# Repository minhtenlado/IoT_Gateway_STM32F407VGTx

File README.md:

# STM32F407 IoT Gateway — 6-Layer PCB

**Custom industrial IoT gateway** based on the **STM32F407VGTx**, designed in **KiCad 10** with Wi-Fi, Ethernet, isolated RS485, four relay outputs, external SPI Flash and an onboard USB-C debug-probe circuit.

> [!IMPORTANT]
> **Trạng thái dự án:** Đã có **schematic, PCB layout 6 lớp, ảnh 3D, Gerber, BOM và mã nguồn firmware debug tham khảo**. Chưa có xác nhận bo mạch đã được lắp ráp, thử nghiệm điện hoặc kiểm chứng đầy đủ ERC/DRC. Không coi các file sản xuất là bằng chứng thiết kế đã sẵn sàng để chế tạo hàng loạt.
>
> **Firmware trong `firrmware_STLINKV2/` là dự án [dap42](https://github.com/devanlai/dap42) (CMSIS-DAP nguồn mở), không phải firmware ST-LINK/V2 chính hãng của STMicroelectronics.** Chưa xác nhận firmware này chạy trên PCB hiện tại mà không chỉnh sửa.

## 1. PCB 3D Preview

Các hình sau được xuất từ **project KiCad của bo mạch này**. Nhấn vào hình để mở ảnh gốc với độ phân giải cao.

### Góc nhìn tổng thể

[.png>)](<images/IoT_gateway_STM32F407(1).png>)

### Hai góc nhìn 3D bổ sung

| 3D View 01 | 3D View 02 |
| :---: | :---: |
|  | [.png>)](<images/IoT_gateway_STM32F407(2).png>) |

## 2. PCB Layout — 6 Copper Layers

PCB sử dụng **6 lớp đồng**: `F.Cu`, `In1.Cu`, `In2.Cu`, `In3.Cu`, `In4.Cu`, `B.Cu`. Các hình bên dưới là ảnh từng lớp riêng biệt, đã lưu trong thư mục [`images/`](images/).

| Front Copper — `F.Cu` | Inner Copper 1 — `In1.Cu` |
| :---: | :---: |
|  |  |

| Inner Copper 2 — `In2.Cu` | Inner Copper 3 — `In3.Cu` |
| :---: | :---: |
|  |  |

| Inner Copper 4 — `In4.Cu` | Back Copper — `B.Cu` |
| :---: | :---: |
|  |  |

### Tổng hợp các lớp đồng

### Bố trí footprint linh kiện

> **Lưu ý:** Các ảnh trên mô tả PCB theo file thiết kế, không phải ảnh bo mạch vật lý đã sản xuất.

## 3. System Architecture

```mermaid
flowchart TB
    PC["Computer"] -->|"USB-C / J2"| DBG["STM32F103CBT6 / U1<br/>Onboard CMSIS-DAP candidate"]
    DBG -. "SWD" .-> MCU["STM32F407VGTx / U3<br/>Main controller"]
    EXT["External SWD probe"] -->|"J1"| MCU
    VIN["12 V DC / J10"] --> POWER["DC/DC power supply"]
    POWER --> MCU
    POWER --> PERI["Peripheral power rails"]
    MCU <-->|"UART"| WIFI["ESP32-C3 Wi-Fi"]
    MCU <-->|"RMII"| ETH["LAN8720A PHY"]
    ETH --- RJ45["RJ45 / J3"]
    MCU <-->|"UART"| RS485["Isolated RS485"]
    MCU --> DRV["ULN2003A"] --> RLY["4 relay channels"]
    MCU <-->|"SPI"| FLASH["W25Q128 Flash"]
    MCU <-->|"I2C / peripherals"| SENS["TMP1075 + INA226"]
    MCU --- GPIO["GPIO headers"]
```

Sơ đồ khối thể hiện **kiến trúc thiết kế**; các giao tiếp chưa được xác nhận hoạt động trên phần cứng thực tế.

## 4. Hardware Overview

| Khối chức năng | Linh kiện / đầu nối | Vai trò |
| --- | --- | --- |
| Main MCU | **U3 — STM32F407VGTx** | Bộ điều khiển trung tâm, ARM Cortex-M4 |
| Onboard debug MCU | **U1 — STM32F103CBT6** | MCU dùng cho mạch USB-to-SWD dự kiến |
| Wireless | **U14 — ESP32-C3-WROOM-02U** | Wi-Fi, giao tiếp với MCU chính |
| Ethernet | **U6 — LAN8720A**, **J3 — HR911105A** | Ethernet PHY 10/100 Mbps và cổng RJ45 |
| Industrial bus | **U10 — ADM2861EBRNZ** | Truyền thông RS485 cách ly |
| Relay outputs | **K1–K4**, **U11 — ULN2003A** | 4 kênh relay có mạch driver |
| External Flash | **U4 — W25Q128JVS** | SPI NOR Flash |
| Temperature | **U12 — TMP1075D** | Giám sát nhiệt độ |
| Power monitoring | **U13 — INA226**, **R56 — 20 mΩ** | Đo điện áp và dòng điện qua shunt |
| RTC backup | **BT1** | Vị trí pin dự phòng |
| Expansion | **J4, J11, J12** | Header GPIO mở rộng |
| System power | **J10** | Nguồn DC 12 V cho hệ thống |
| Debug USB | **J2** | USB Type-C kết nối với U1 |
| External programming | **J1** | Header SWD nạp trực tiếp U3 |

### Power architecture

Các khối nguồn trên schematic gồm **AP63203WU (U7)**, **AP63205WU (U8)** và **AP2112K-3.3 (U9)**. Các net chính bao gồm `+12V_PROTECTED`, `+5V_BUCK`, `+3V3_SYS` và `+3V3_STLINK`.

> [!WARNING]
> **USB-C/J2 không được mặc định là nguồn cấp cho toàn bộ bo mạch.** Theo cấu trúc hiện tại, J2 phục vụ khối debug U1, còn U3 và hệ thống cần nguồn phù hợp từ đường DC 12 V. Phải kiểm tra sơ đồ nguồn trước khi nạp/debug hoặc nối nguồn đồng thời.

## 5. STM32 Programming & Debugging

Có **hai đường nạp/debug khác nhau** cho STM32F407 (U3).

### A. External ST-Link / CMSIS-DAP via J1

**J1 là cổng SWD dành cho U3 (STM32F407VGTx), không phải cổng nạp U1.**

| SWD signal | Target U3 |
| --- | --- |
| SWDIO / `T_DIO` | PA13 |
| SWCLK / `T_CLK` | PA14 |
| NRST / `T_RST` | NRST |
| GND | GND |
| VTref | 3.3 V target logic reference |

Cấp nguồn cho bo mạch theo thiết kế, sau đó kết nối một probe SWD bên ngoài với **J1 theo tên net trên schematic**. Dùng **STM32CubeProgrammer** với ST-Link chính hãng hoặc phần mềm tương thích với probe đang sử dụng. Không suy luận thứ tự chân J1 từ bảng này.

### B. Onboard USB-C debug via J2 and U1

Đường tín hiệu dự kiến:

`Computer → USB-C (J2) → STM32F103CBT6 (U1) → SWD → STM32F407VGTx (U3)`

| SWD signal | U1 — Debug MCU | U3 — Main MCU |
| --- | --- | --- |
| SWDIO / `T_DIO` | PB14 | PA13 |
| SWCLK / `T_CLK` | PB13 | PA14 |
| Reset / `T_RST` | PB0 | NRST |
| SWO / `T_SWO` | PA10 (theo schematic) | PB3 |

Để mạch debug onboard hoạt động, cần nạp và cấu hình firmware thích hợp vào U1, bảo đảm clock USB/SWD, reset, pin mapping và nguồn logic. **Không thể chỉ hàn STM32F103 mới lên PCB rồi cắm USB-C để máy tính tự nhận ST-Link.**

## 6. Onboard Debugger Firmware — dap42 / CMSIS-DAP

Mã nguồn được lưu tại [`firrmware_STLINKV2/`](firrmware_STLINKV2/) (**giữ nguyên tên thư mục hiện tại, bao gồm cách viết `firrmware`**).

> [!IMPORTANT]
> Thư mục trên chứa **[dap42](https://github.com/devanlai/dap42)**, một dự án **CMSIS-DAP open-source** hỗ trợ STM32F042/STM32F103 và có các cấu hình dành cho **phần cứng ST-LINK/V2 hoặc ST-LINK/V2-1**. Tên thư mục không có nghĩa đây là firmware ST-LINK/V2 chính hãng. Sau khi nạp dap42, probe hoạt động theo giao thức **CMSIS-DAP** (ví dụ với OpenOCD), **không phải thiết bị ST-Link chính hãng trong STM32CubeProgrammer**.

### Những gì có sẵn trong thư mục firmware

| Đường dẫn | Nội dung |
| --- | --- |
| [`firrmware_STLINKV2/src/`](firrmware_STLINKV2/src/) | Mã nguồn C cho CMSIS-DAP, USB, cấu hình phần cứng |
| [`firrmware_STLINKV2/src/targets.mk`](firrmware_STLINKV2/src/targets.mk) | Các target STM32F103, STLINKV2-DONGLE, STLINKV2-1 |
| [`firrmware_STLINKV2/Makefile`](firrmware_STLINKV2/Makefile) | Build targets và xuất firmware `.bin` |
| [`firrmware_STLINKV2/openocd/`](firrmware_STLINKV2/openocd/) | Cấu hình OpenOCD tham khảo |
| [`firrmware_STLINKV2/FLASHING.md`](firrmware_STLINKV2/FLASHING.md) | Hướng dẫn nạp firmware dap42 |
| [`firrmware_STLINKV2/README.md`](firrmware_STLINKV2/README.md) | Tài liệu dự án dap42 gốc |
| [`firrmware_STLINKV2/LICENSE`](firrmware_STLINKV2/LICENSE) | Giấy phép phần mềm của dự án dap42 |

**Khả năng phù hợp với PCB này:** Các đường `PB14 → SWDIO`, `PB13 → SWCLK` và `PB0 → NRST` của U1 tương ứng với cấu hình STM32F103 kiểu `stlinkv2-1` trong dap42. **Tuy nhiên, đường SWO trên schematic là `PA10` trong khi cấu hình mẫu dùng `PB11`;** ngoài ra còn phải kiểm tra USB pull-up, LED, GPIO khác và 8 MHz HSE trước khi flash. Chưa có bản firmware được chứng minh là tương thích toàn bộ pinout của PCB.

### Build firmware (tham khảo, chưa xác nhận cho PCB này)

Mã nguồn dap42 dùng **libopencm3**. Bản RAR được cung cấp **chưa chứa mã nguồn dependency này** trong thư mục `libopencm3/`; cần tải bổ sung trước khi build:

```bash
cd firrmware_STLINKV2
# Chỉ cần thực hiện khi thư mục libopencm3 chưa có mã nguồn
git clone https://github.com/libopencm3/libopencm3.git libopencm3

# Yêu cầu: GNU make và ARM GNU Toolchain (arm-none-eabi-*)
# Build ví dụ cho phần cứng profile ST-LINK/V2-1 tham khảo:
make DAP103-NUCLEO.bin
```

Bản `.bin` sinh ra bởi lệnh trên **không được khuyến nghị nạp trực tiếp lên U1** trước khi đối chiếu và điều chỉnh file `src/stm32f103/stlinkv2-1/target.c`, `config.h`, thiết lập clock và chân của PCB. Cần phương pháp **nạp lần đầu cho U1** bằng SWD hoặc bootloader thích hợp; **J1 chỉ phục vụ U3**.

**Upstream & licensing:** [devanlai/dap42](https://github.com/devanlai/dap42) · [dap42 hardware](https://github.com/devanlai/dap42-hardware) · [libopencm3](https://github.com/libopencm3/libopencm3). Mã nguồn bao gồm thành phần mang giấy phép ISC, Apache-2.0 và LGPLv3; khi phân phối phải tuân thủ các giấy phép kèm theo từng thành phần.

## 7. ESP32-C3 Wi-Fi

Module **ESP32-C3-WROOM-02U** cung cấp chức năng Wi-Fi. Header **J13 (`ESP32_UART0_PROG`)** trên schematic phục vụ UART0 để lập trình và kiểm tra module. Khi sử dụng bộ chuyển USB–UART ngoài, phải kiểm tra điện áp logic 3.3 V và chế độ boot thực tế.

## 8. Project Structure

```text
IoT_gateway_STM32F407/
├── README.md
├── IoT_gateway_STM32F407.kicad_pro      # KiCad project
├── IoT_gateway_STM32F407.kicad_sch      # Schematic
├── IoT_gateway_STM32F407.kicad_pcb      # 6-layer PCB layout
├── Schematic.pdf                       # PDF schematic
├── images/
│   ├── IoT_gateway_STM32F407.png       # 3D render
│   ├── IoT_gateway_STM32F407(1).png    # 3D render
│   ├── IoT_gateway_STM32F407(2).png    # 3D render
│   ├── F_cu.png
│   ├── In1_cu.png
│   ├── In2_cu.png
│   ├── In3_cu.png
│   ├── In4_cu.png
│   ├── B_cu.png
│   ├── F_in1_in2_in3_in4_B.png          # All layers preview
│   └── footprint.png                   # Component placement
├── production/
│   ├── IoT_gateway_STM32F407.zip       # Gerber + drill package
│   ├── bom.csv
│   ├── positions.csv
│   ├── designators.csv
│   └── netlist.ipc
├── firrmware_STLINKV2/                 # dap42 CMSIS-DAP source
│   ├── src/
│   ├── openocd/
│   ├── Makefile
│   ├── FLASHING.md
│   ├── LICENSE
│   └── README.md
└── library/                            # Custom symbols/footprints/models
```

### Quick links

- **[Mở thiết kế PCB KiCad](IoT_gateway_STM32F407.kicad_pcb)**
- **[Mở schematic KiCad](IoT_gateway_STM32F407.kicad_sch)** · **[Xem schematic PDF](Schematic.pdf)**
- **[Tải bộ Gerber + Drill](production/IoT_gateway_STM32F407.zip)**
- **[Xem BOM](production/bom.csv)** · **[Component placement](production/positions.csv)**
- **[Xem mã nguồn firmware CMSIS-DAP](firrmware_STLINKV2/)**
- **[Xem toàn bộ ảnh PCB](images/)**

## 9. Verification Checklist

- [x] Schematic được lưu trong project KiCad.
- [x] PCB layout **6 copper layers** đã có trong repository.
- [x] Đã xuất 3 ảnh 3D, 6 lớp đồng và 2 ảnh bổ sung.
- [x] Đã xuất Gerber/Drill, BOM và component placement files.
- [x] Có mã nguồn **dap42 CMSIS-DAP** làm firmware tham khảo cho U1.
- [x] Hoàn tất và xác nhận **ERC/DRC**, clearance, copper stackup, lớp cách ly.
- [ ] Kiểm tra đường nguồn 12 V, 5 V, 3.3 V và tách nguồn USB debug.
- [ ] Kiểm chứng thạch anh, USB, pin mapping và firmware CMSIS-DAP cho U1.
- [ ] Kiểm chứng Ethernet RMII/PHY, Wi-Fi, RS485, relay và cảm biến.
- [ ] Xác nhận quy trình nạp/khôi phục U1; thử nạp U3 qua U1 và qua debug onboard.
- [ ] Lắp prototype và thực hiện kiểm thử phần cứng trước khi sản xuất hàng loạt.

## 10. Safety & Licensing

- Không kết nối điện lưới AC hoặc tải công suất vào relay trước khi kiểm tra **clearance/creepage, cách ly, bảo vệ quá dòng, định mức relay và vỏ bảo vệ**.
- GPIO, UART, SWD phải dùng mức điện áp tương thích; không cấp 5 V vào chân logic 3.3 V nếu không được cho phép.
- File Gerber được cung cấp như **tài liệu thiết kế**, chưa phải chứng nhận đủ điều kiện sản xuất an toàn.
- **Phần cứng:** Chưa có file `LICENSE` riêng xác nhận giấy phép phát hành thiết kế PCB/schematic. Việc đăng lên GitHub không tự động chuyển quyền sử dụng phần cứng thành open-source hardware.
- **Firmware dap42:** Giữ nguyên thông báo bản quyền và các điều khoản trong [`firrmware_STLINKV2/LICENSE`](firrmware_STLINKV2/LICENSE) cũng như giấy phép thành phần phụ thuộc. Không hiểu nhầm đây là firmware chính hãng của ST.

---

**Designed by Phan Huynh Van Do** · **HW Rev 1.0 (design marking)** · **2026**

*STM32F407 IoT Gateway — custom embedded hardware for connected control and industrial interfaces.*

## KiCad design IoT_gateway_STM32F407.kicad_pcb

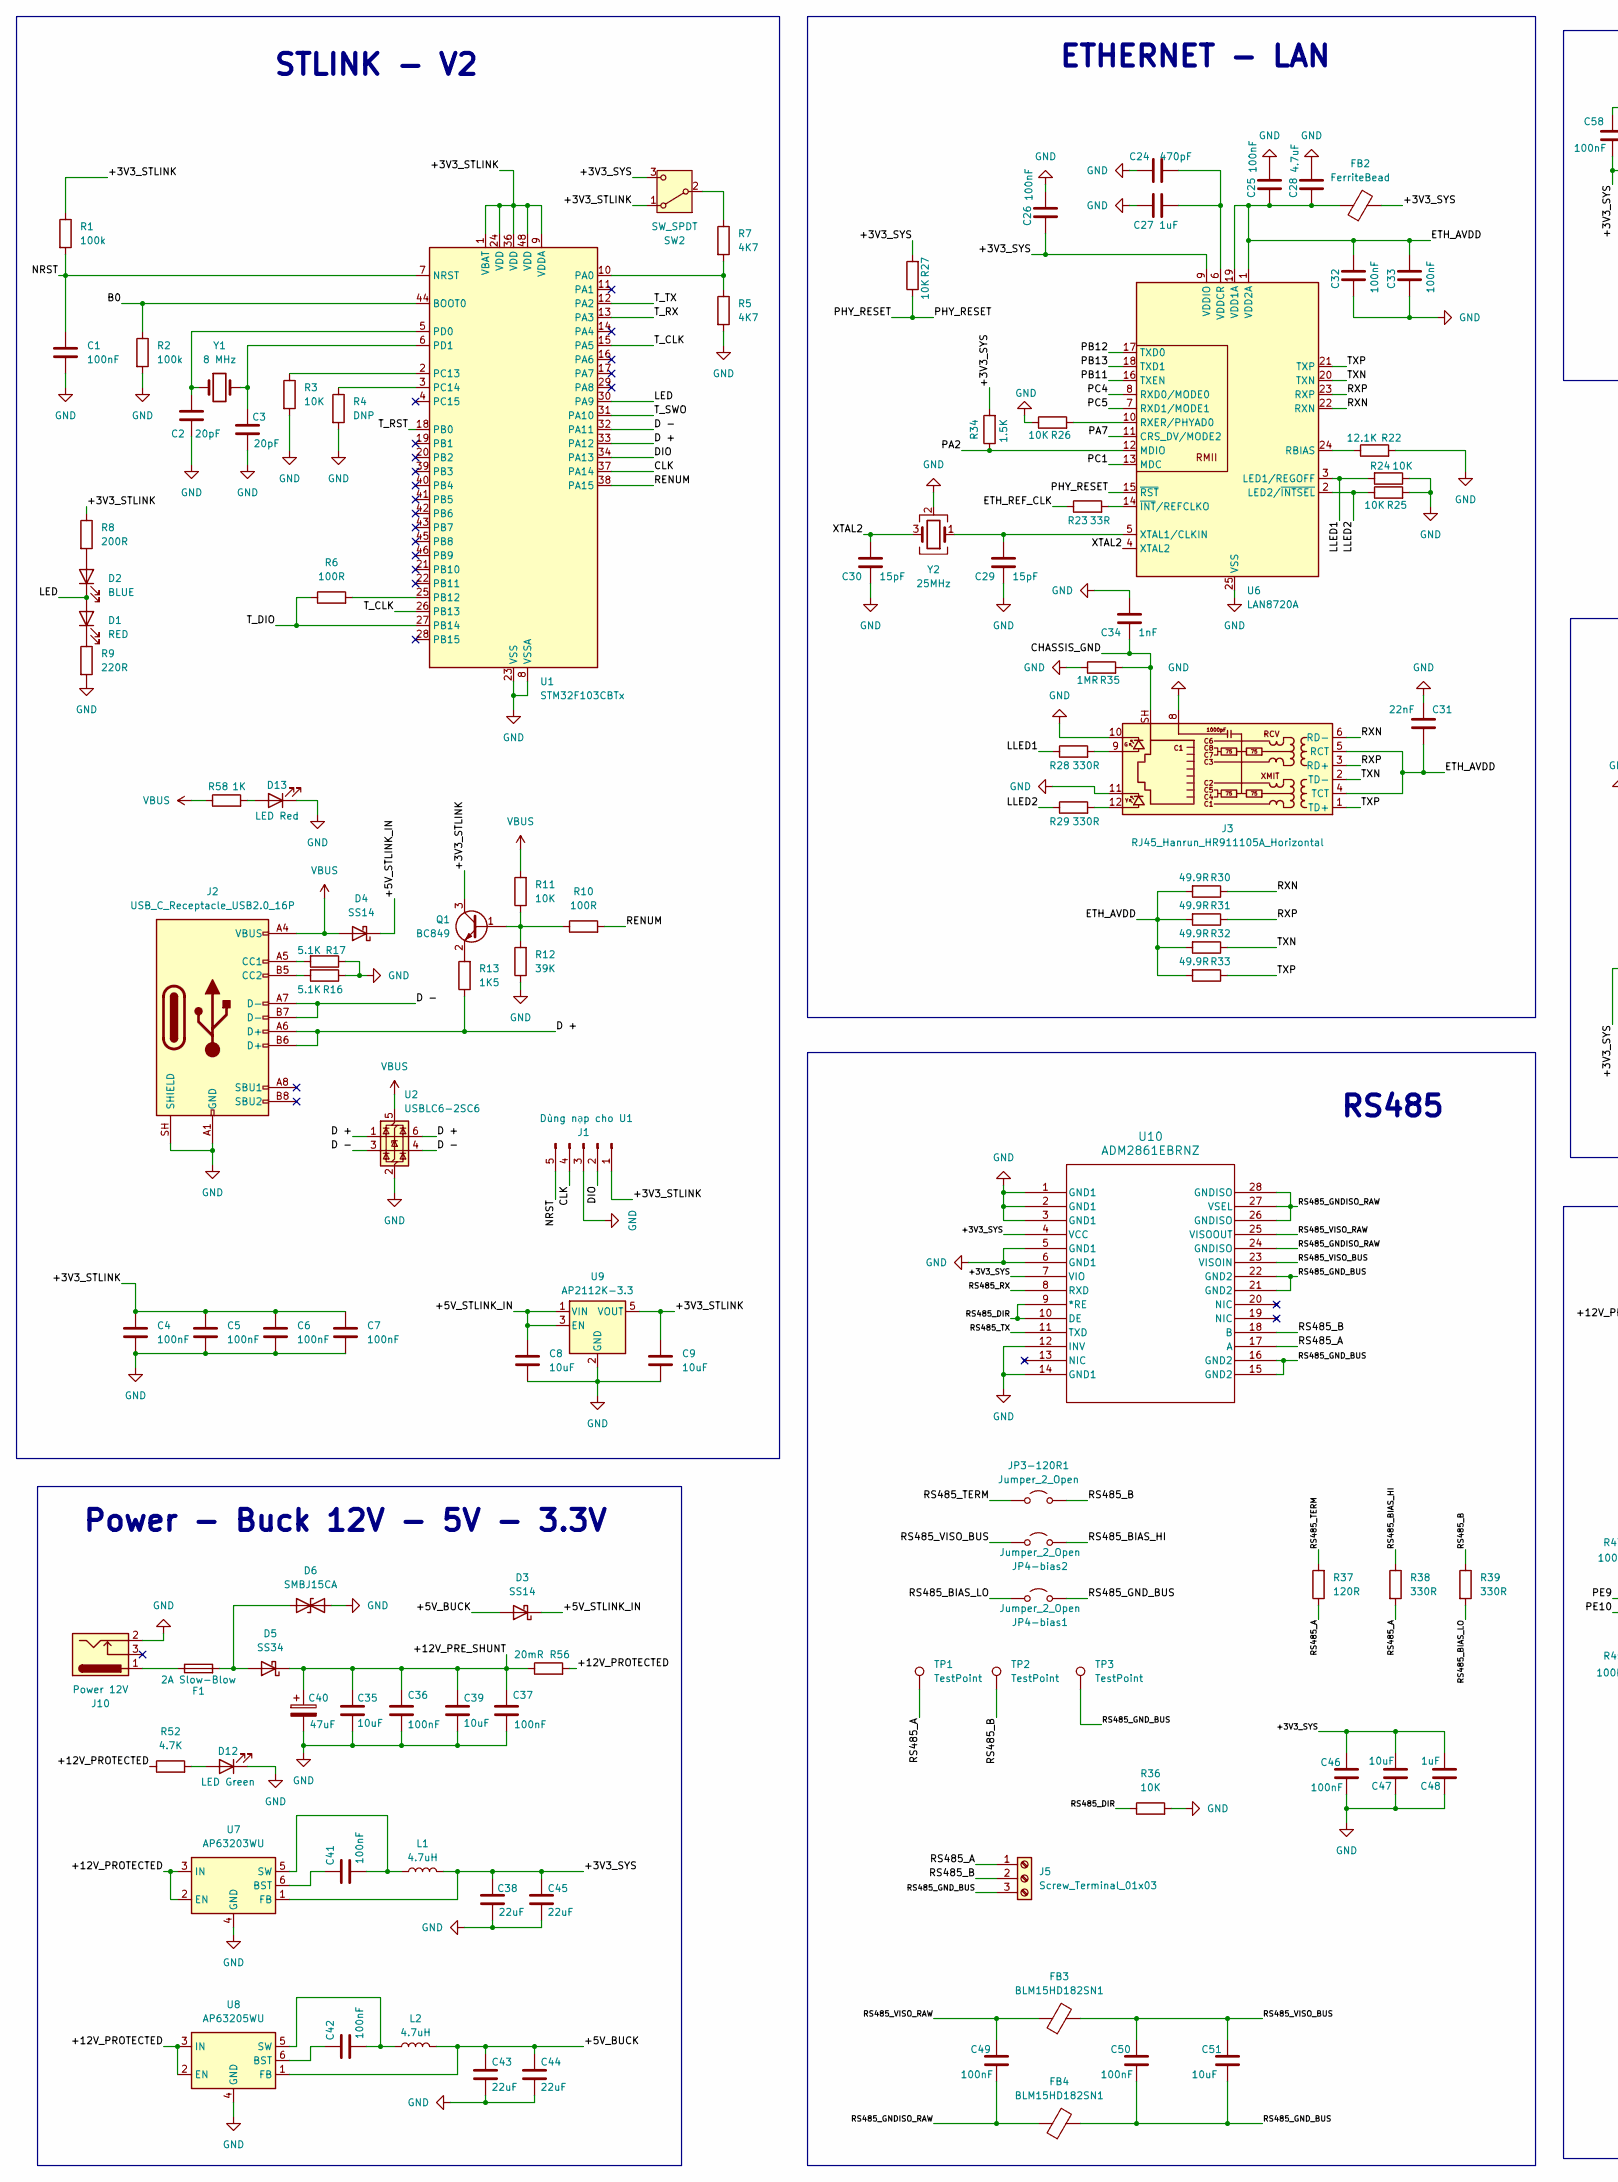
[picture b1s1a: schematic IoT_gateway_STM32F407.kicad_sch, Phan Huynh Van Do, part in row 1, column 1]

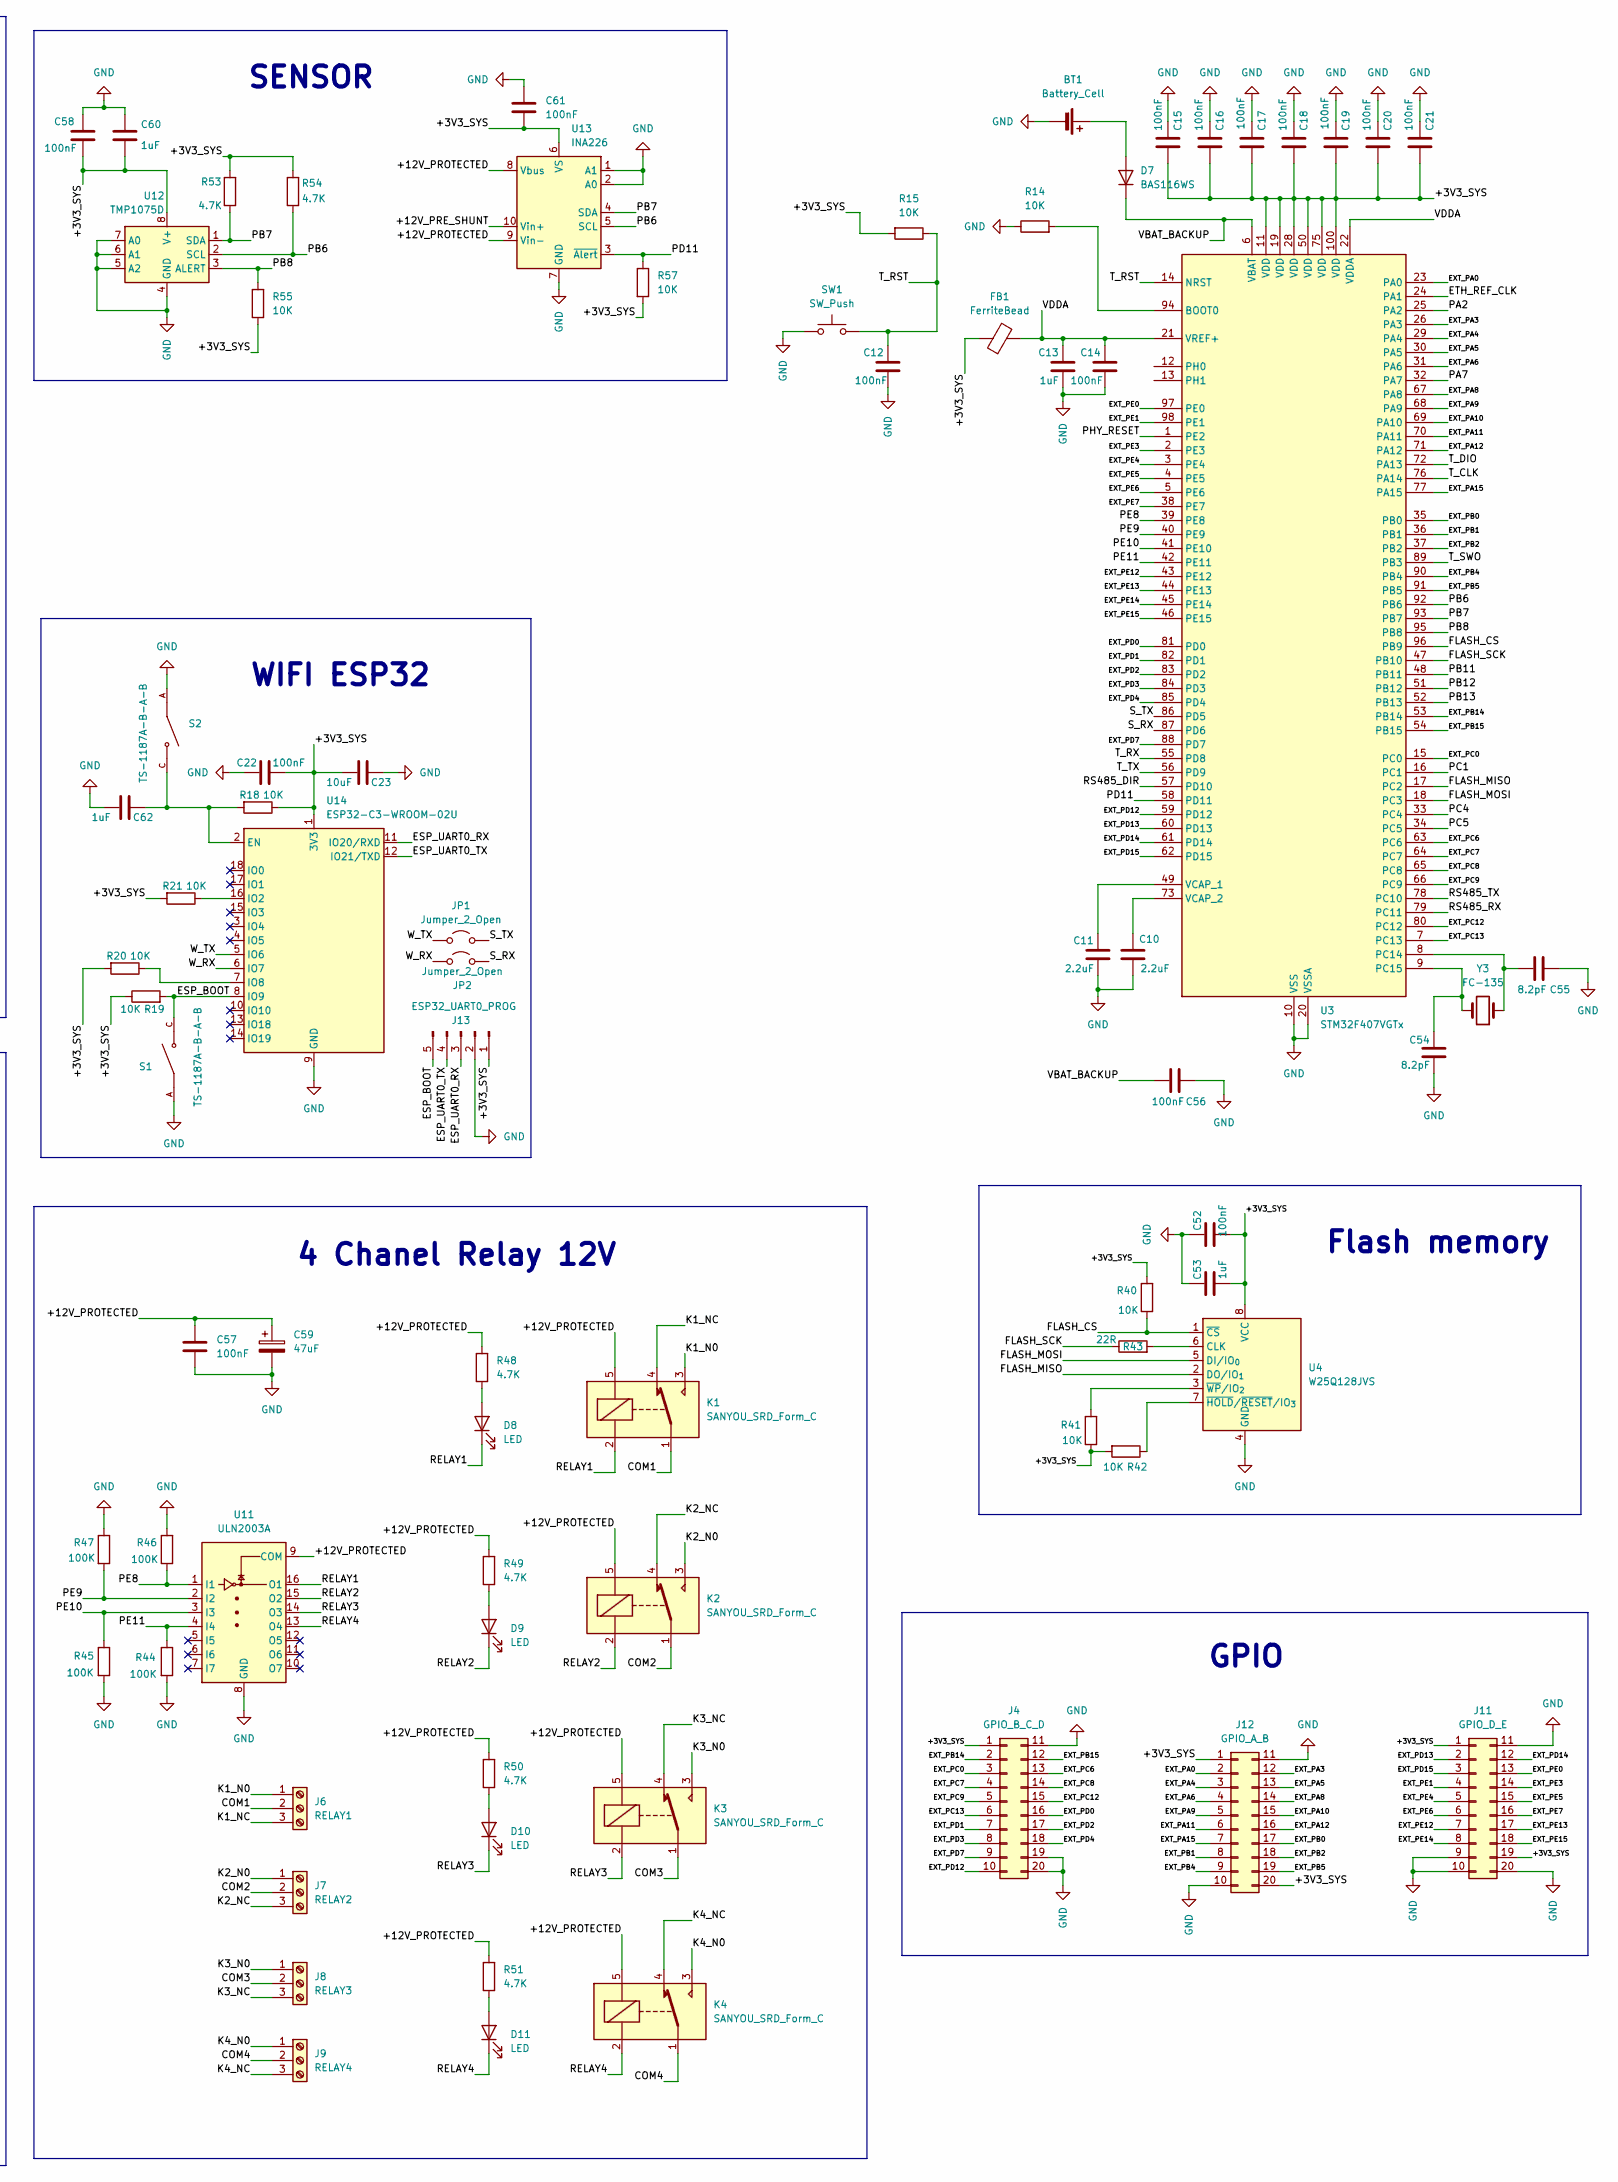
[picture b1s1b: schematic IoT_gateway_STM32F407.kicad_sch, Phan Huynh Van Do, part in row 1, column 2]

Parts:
BT1: Battery_Cell; BatteryHolder_Keystone_3034_1x20mm
C1, C4, C5, C6, C7, C12, C14, C15, C16, C17, C18, C19, C20, C21, C22, C25, C26, C32, C33, C36, C37, C41, C42: 100nF; C_0603_1608Metric
C2, C3: 20pF; C_0603_1608Metric
C8, C9, C23: 10uF; C_0603_1608Metric
C10, C11: 2.2uF; C_0603_1608Metric
C13, C27, C62: 1uF; C_0603_1608Metric
C24: 470pF; C_0603_1608Metric
C28: 4.7uF; C_0603_1608Metric
C29, C30: 15pF; C_0603_1608Metric
C31: 22nF; C_0603_1608Metric
C34: 1nF; C_0603_1608Metric
C35: 10uF; C_1210_3225Metric
C38, C43, C44, C45: 22uF; C_1210_3225Metric
C39: 10uF; C_0805_2012Metric
C40, C59: 47uF; CP_Radial_D6.3mm_P2.50mm
C46, C49, C50, C52, C56, C57, C58, C61: 100nF; C_0805_2012Metric
C47, C51: 10uF; C_1206_3216Metric
C48, C53, C60: 1uF; C_0805_2012Metric
C54: 8.2pF; C_0603_1608Metric
C55: 8.2pF; C_0805_2012Metric
D1: RED; LED_0603_1608Metric
D2: BLUE; LED_0603_1608Metric
D3, D4: SS14; D_SMA
D5: SS34; D_SMA
D6: SMBJ15CA; D_SMB
D7: BAS116WS; D_SOD-323
D8, D9, D10, D11: LED; LED_0805_2012Metric
D12: LED Green; LED_0805_2012Metric
D13: LED Red; LED_0805_2012Metric
F1: 2A Slow-Blow; Fuse_1206_3216Metric
FB1, FB2: FerriteBead; L_0603_1608Metric
FB3, FB4: BLM15HD182SN1; L_0402_1005Metric
J1: Dùng nạp cho U1; PinHeader_1x05_P2.54mm_Vertical
J2: USB_C_Receptacle_USB2.0_16P; USB_C_Receptacle_HRO_TYPE-C-31-M-12
J3: RJ45_Hanrun_HR911105A_Horizontal
J4: GPIO_B_C_D; PinHeader_2x10_P2.54mm_Vertical
J5: Screw_Terminal_01x03; TerminalBlock_Phoenix_MKDS-1,5-3-5.08_1x03_P5.08mm_Horizont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
J6: RELAY1; TerminalBlock_Phoenix_MKDS-3-3-5.08_1x03_P5.08mm_Horizontal
J7: RELAY2; TerminalBlock_Phoenix_MKDS-3-3-5.08_1x03_P5.08mm_Horizontal
J8: RELAY3; TerminalBlock_Phoenix_MKDS-3-3-5.08_1x03_P5.08mm_Horizontal
J9: RELAY4; TerminalBlock_Phoenix_MKDS-3-3-5.08_1x03_P5.08mm_Horizontal
J10: Power 12V; BarrelJack_CUI_PJ-102AH_Horizontal
J11: GPIO_D_E; PinHeader_2x10_P2.54mm_Vertical
J12: GPIO_A_B; PinHeader_2x10_P2.54mm_Vertical
J13: ESP32_UART0_PROG; PinHeader_1x05_P2.54mm_Vertical
JP1, JP2, JP3-120R1, JP4-bias1, JP4-bias2: Jumper_2_Open; PinHeader_1x02_P2.54mm_Vertical
K1, K2, K3, K4: SANYOU_SRD_Form_C; Relay_SPDT_SANYOU_SRD_Series_Form_C
L1, L2: 4.7uH; L_Bourns_SRN6045TA
Q1: BC849; SOT-23
R1, R2: 100k; R_0603_1608Metric
R3, R11, R14, R15, R18, R19, R20, R21, R24, R25, R26, R27: 10K; R_0603_1608Metric
R4: DNP; R_0603_1608Metric
R5, R7: 4K7; R_0603_1608Metric
R6, R10: 100R; R_0603_1608Metric
R8: 200R; R_0603_1608Metric
R9: 220R; R_0603_1608Metric
R12: 39K; R_0603_1608Metric
R13: 1K5; R_0603_1608Metric
R16, R17: 5.1K; R_0603_1608Metric
R22: 12.1K; R_0603_1608Metric
R23: 33R; R_0603_1608Metric
R28, R29: 330R; R_0603_1608Metric
R30, R31, R32, R33: 49.9R; R_0603_1608Metric
R34: 1.5K; R_0603_1608Metric
R35: 1MR; R_0603_1608Metric
R36, R40, R41, R42, R55, R57: 10K; R_0805_2012Metric
R37: 120R; R_1206_3216Metric
R38, R39: 330R; R_0805_2012Metric
R43: 22R; R_0805_2012Metric
R44, R45, R46, R47: 100K; R_0805_2012Metric
R48, R49, R50, R51, R52, R53, R54: 4.7K; R_0805_2012Metric
R56: 20mR; R_2512_6332Metric
R58: 1K; R_0805_2012Metric
S1, S2: TS-1187A-B-A-B; SW_TS-1187A-B-A-B; PARTREV A0
SW1: SW_Push; SW_PUSH-12mm
SW2: SW_SPDT; SW_Slide_SPDT_Straight_CK_OS102011MS2Q
TP1, TP2, TP3: TestPoint; TestPoint_Pad_D1.5mm
U1: STM32F103CBTx; LQFP-48_7x7mm_P0.5mm
U2: USBLC6-2SC6; SOT-23-6
U3: STM32F407VGTx; LQFP-100_14x14mm_P0.5mm
U4: W25Q128JVS; SOIC-8_5.3x5.3mm_P1.27mm
U6: LAN8720A; VQFN-24-1EP_4x4mm_P0.5mm_EP2.5x2.5mm_ThermalVias
U7: AP63203WU; TSOT-23-6
U8: AP63205WU; TSOT-23-6
U9: AP2112K-3.3; SOT-23-5
U10: ADM2861EBRNZ; RN-28-1_ADI-L
U11: ULN2003A; SOIC-16_3.9x9.9mm_P1.27mm
U12: TMP1075D; SO-8_3.9x4.9mm_P1.27mm
U13: INA226; TSSOP-10_3x3mm_P0.5mm
U14: ESP32-C3-WROOM-02U
Y1: 8 MHz; Crystal_SMD_ECS_CSM3X-2Pin_7.6x4.1mm
Y2: 25MHz; Crystal_SMD_3225-4Pin_3.2x2.5mm
Y3: FC-135; Crystal_SMD_3215-2Pin_3.2x1.5mm

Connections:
/+3V3_STLINK: C4.2, C5.2, C6.2, C7.2, C9.2, J1.1, Q1.3 (C), R1.1, R8.1, SW2.1 (A), U1.1 (VBAT), U1.9 (VDDA), U1.24 (VDD), U1.36 (VDD), U1.48 (VDD), U9.5 (VOUT)
/+3V3_SYS: C15.2, C16.2, C17.2, C18.2, C19.2, C20.2, C21.2, C22.1, C23.1, C26.1, C38.1, C45.1, C46.1, C47.2, C48.2, C52.2, C53.2, C58.2, C60.2, C61.2, FB1.1, FB2.2, J4.1, J11.1, J11.19, J12.1, J12.20, J13.1, L1.2, R15.2, R18.1, R19.1, R20.2, R21.2, R27.2, R34.2, R40.2, R41.1, R42.2, R53.2, R54.2, R55.1, R57.2, SW2.3 (C), U3.11 (VDD), U3.19 (VDD), U3.28 (VDD), U3.50 (VDD), U3.75 (VDD), U3.100 (VDD), U4.8 (VCC), U6.9 (VDDIO), U7.1 (FB), U10.4 (VCC), U10.7 (VIO), U12.8 (V+), U13.6 (VS), U14.1 (3V3)
/+5V_BUCK: C43.1, C44.1, D3.2 (A), L2.2, U8.1 (FB)
/+5V_STLINK_IN: C8.2, D3.1 (K), D4.1 (K), U9.1 (VIN), U9.3 (EN)
/+12V_PRE_SHUNT: C35.1, C36.1, C37.1, C39.1, C40.1, D5.1 (K), R56.1, U13.10 (Vin+)
/+12V_PROTECTED: C57.1, C59.1, K1.5, K2.5, K3.5, K4.5, R48.2, R49.2, R50.2, R51.2, R52.1, R56.2, U7.2 (EN), U7.3 (IN), U8.2 (EN), U8.3 (IN), U11.9 (COM), U13.8 (Vbus), U13.9 (Vin-)
/B0: R2.1, U1.44 (BOOT0)
/CHASSIS_GND: C34.1, J3.SH, R35.2
/CLK: J1.4, U1.37 (PA14)
/COM1: J6.2, K1.1
/COM2: J7.2, K2.1
/COM3: J8.2, K3.1
/COM4: J9.2, K4.1
/D +: J2.A6 (D+), J2.B6 (D+), R13.1, U1.33 (PA12), U2.1 (I/O1), U2.6 (I/O1)
/D -: J2.A7 (D-), J2.B7 (D-), U1.32 (PA11), U2.3 (I/O2), U2.4 (I/O2)
/DIO: J1.2, U1.34 (PA13)
/ESP_BOOT: J13.5, R19.2, S1.C, S1.D, U14.8 (IO9)
/ESP_UART0_RX: J13.3, U14.11 (IO20/RXD)
/ESP_UART0_TX: J13.4, U14.12 (IO21/TXD)
/ETH_AVDD: C25.1, C28.1, C31.2, C32.2, C33.2, FB2.1, J3.4 (TCT), J3.5 (RCT), R30.2, R31.2, R32.2, R33.2, U6.1 (VDD2A), U6.19 (VDD1A)
/ETH_REF_CLK: R23.1, U3.24 (PA1)
/EXT_PA0: J12.2, U3.23 (PA0)
/EXT_PA3: J12.12, U3.26 (PA3)
/EXT_PA4: J12.3, U3.29 (PA4)
/EXT_PA5: J12.13, U3.30 (PA5)
/EXT_PA6: J12.4, U3.31 (PA6)
/EXT_PA8: J12.14, U3.67 (PA8)
/EXT_PA9: J12.5, U3.68 (PA9)
/EXT_PA10: J12.15, U3.69 (PA10)
/EXT_PA11: J12.6, U3.70 (PA11)
/EXT_PA12: J12.16, U3.71 (PA12)
/EXT_PA15: J12.7, U3.77 (PA15)
/EXT_PB0: J12.17, U3.35 (PB0)
/EXT_PB1: J12.8, U3.36 (PB1)
/EXT_PB2: J12.18, U3.37 (PB2)
/EXT_PB4: J12.9, U3.90 (PB4)
/EXT_PB5: J12.19, U3.91 (PB5)
/EXT_PB14: J4.2, U3.53 (PB14)
/EXT_PB15: J4.12, U3.54 (PB15)
/EXT_PC0: J4.3, U3.15 (PC0)
/EXT_PC6: J4.13, U3.63 (PC6)
/EXT_PC7: J4.4, U3.64 (PC7)
/EXT_PC8: J4.14, U3.65 (PC8)
/EXT_PC9: J4.5, U3.66 (PC9)
/EXT_PC12: J4.15, U3.80 (PC12)
/EXT_PC13: J4.6, U3.7 (PC13)
/EXT_PD0: J4.16, U3.81 (PD0)
/EXT_PD1: J4.7, U3.82 (PD1)
/EXT_PD2: J4.17, U3.83 (PD2)
/EXT_PD3: J4.8, U3.84 (PD3)
/EXT_PD4: J4.18, U3.85 (PD4)
/EXT_PD7: J4.9, U3.88 (PD7)
/EXT_PD12: J4.10, U3.59 (PD12)
/EXT_PD13: J11.2, U3.60 (PD13)
/EXT_PD14: J11.12, U3.61 (PD14)
/EXT_PD15: J11.3, U3.62 (PD15)
/EXT_PE0: J11.13, U3.97 (PE0)
/EXT_PE1: J11.4, U3.98 (PE1)
/EXT_PE3: J11.14, U3.2 (PE3)
/EXT_PE4: J11.5, U3.3 (PE4)
/EXT_PE5: J11.15, U3.4 (PE5)
/EXT_PE6: J11.6, U3.5 (PE6)
/EXT_PE7: J11.16, U3.38 (PE7)
/EXT_PE12: J11.7, U3.43 (PE12)
/EXT_PE13: J11.17, U3.44 (PE13)
/EXT_PE14: J11.8, U3.45 (PE14)
/EXT_PE15: J11.18, U3.46 (PE15)
/FLASH_CS: R40.1, U3.96 (PB9), U4.1 (~CS)
/FLASH_MISO: U3.17 (PC2), U4.2 (DO/IO_{1})
/FLASH_MOSI: U3.18 (PC3), U4.5 (DI/IO_{0})
/FLASH_SCK: R43.1, U3.47 (PB10)
/K1_N0: J6.1, K1.3
/K1_NC: J6.3, K1.4
/K2_N0: J7.1, K2.3
/K2_NC: J7.3, K2.4
/K3_N0: J8.1, K3.3
/K3_NC: J8.3, K3.4
/K4_N0: J9.1, K4.3
/K4_NC: J9.3, K4.4
/LED: D1.2 (A), D2.1 (K), U1.30 (PA9)
/LLED1: R24.2, R28.1, U6.3 (LED1/REGOFF)
/LLED2: R25.1, R29.1, U6.2 (LED2/~INTSEL)
/NRST: C1.1, J1.5, R1.2, U1.7 (NRST)
/PA2: R34.1, U3.25 (PA2), U6.12 (MDIO)
/PA7: U3.32 (PA7), U6.11 (CRS_DV/MODE2)
/PB6: R54.1, U3.92 (PB6), U12.2 (SCL), U13.5 (SCL)
/PB7: R53.1, U3.93 (PB7), U12.1 (SDA), U13.4 (SDA)
/PB8: R55.2, U3.95 (PB8), U12.3 (ALERT)
/PB11: U3.48 (PB11), U6.16 (TXEN)
/PB12: U3.51 (PB12), U6.17 (TXD0)
/PB13: U3.52 (PB13), U6.18 (TXD1)
/PC1: U3.16 (PC1), U6.13 (MDC)
/PC4: U3.33 (PC4), U6.8 (RXD0/MODE0)
/PC5: U3.34 (PC5), U6.7 (RXD1/MODE1)
/PD11: R57.1, U3.58 (PD11), U13.3 (~Alert)
/PE8: R46.1, U3.39 (PE8), U11.1 (I1)
/PE9: R47.2, U3.40 (PE9), U11.2 (I2)
/PE10: R45.1, U3.41 (PE10), U11.3 (I3)
/PE11: R44.1, U3.42 (PE11), U11.4 (I4)
/PHY_RESET: R27.1, U3.1 (PE2), U6.15 (~RST)
/RELAY1: D8.1 (K), K1.2, U11.16 (O1)
/RELAY2: D9.1 (K), K2.2, U11.15 (O2)
/RELAY3: D10.1 (K), K3.2, U11.14 (O3)
/RELAY4: D11.1 (K), K4.2, U11.13 (O4)
/RENUM: R10.2, U1.38 (PA15)
/RS485_A: J5.1, R37.1, R38.2, TP1.1 (1_1), U10.17 (A)
/RS485_B: J5.2, JP3-120R1.2 (B), R39.1, TP2.1 (1_1), U10.18 (B)
/RS485_BIAS_HI: JP4-bias2.2 (B), R38.1
/RS485_BIAS_LO: JP4-bias1.1 (A), R39.2
/RS485_DIR: R36.1, U3.57 (PD10), U10.9 (*RE), U10.10 (DE)
/RS485_GNDISO_RAW: C49.2, FB4.1, U10.24 (GNDISO), U10.26 (GNDISO), U10.27 (VSEL), U10.28 (GNDISO)
/RS485_GND_BUS: C50.2, C51.2, FB4.2, J5.3, JP4-bias1.2 (B), TP3.1 (1_1), U10.15 (GND2), U10.16 (GND2), U10.21 (GND2), U10.22 (GND2)
/RS485_RX: U3.79 (PC11), U10.8 (RXD)
/RS485_TERM: JP3-120R1.1 (A), R37.2
/RS485_TX: U3.78 (PC10), U10.11 (TXD)
/RS485_VISO_BUS: C50.1, C51.1, FB3.2, JP4-bias2.1 (A), U10.23 (VISOIN)
/RS485_VISO_RAW: C49.1, FB3.1, U10.25 (VISOOUT)
/RXN: J3.6 (RD-), R30.1, U6.22 (RXN)
/RXP: J3.3 (RD+), R31.1, U6.23 (RXP)
/S_RX: JP2.2 (B), U3.87 (PD6)
/S_TX: JP1.2 (B), U3.86 (PD5)
/TXN: J3.2 (TD-), R32.1, U6.20 (TXN)
/TXP: J3.1 (TD+), R33.1, U6.21 (TXP)
/T_CLK: U1.15 (PA5), U1.26 (PB13), U3.76 (PA14)
/T_DIO: R6.1, U1.27 (PB14), U3.72 (PA13)
/T_RST: C12.1, R15.1, SW1.2, U1.18 (PB0), U3.14 (NRST)
/T_RX: U1.13 (PA3), U3.55 (PD8)
/T_SWO: U1.31 (PA10), U3.89 (PB3)
/T_TX: U1.12 (PA2), U3.56 (PD9)
/VBAT_BACKUP: C56.2, D7.1 (K), U3.6 (VBAT)
/VDDA: C13.1, C14.1, FB1.2, U3.21 (VREF+), U3.22 (VDDA)
/W_RX: JP2.1 (A), U14.6 (IO7)
/W_TX: JP1.1 (A), U14.5 (IO6)
/XTAL2: C30.2, U6.4 (XTAL2), Y2.3
GND: BT1.2 (-), C1.2, C2.2, C3.2, C4.1, C5.1, C6.1, C7.1, C8.1, C9.1, C10.2, C11.2, C12.2, C13.2, C14.2, C15.1, C16.1, C17.1, C18.1, C19.1, C20.1, C21.1, C22.2, C23.2, C24.1, C25.2, C26.2, C27.1, C28.2, C29.1, C30.1, C31.1, C32.1, C33.1, C34.2, C35.2, C36.2, C37.2, C38.2, C39.2, C40.2, C43.2, C44.2, C45.2, C46.2, C47.1, C48.1, C52.1, C53.1, C54.2, C55.1, C56.1, C57.2, C58.1, C59.2, C60.1, C61.1, C62.1, D6.2 (A2), D12.1 (K), D13.1 (K), J1.3, J2.A1 (GND), J2.A12 (GND), J2.B1 (GND), J2.B12 (GND), J2.SH (SHIELD), J3.8, J3.10, J3.11, J4.11, J4.19, J4.20, J10.2, J11.9, J11.10, J11.11, J11.20, J12.10, J12.11, J13.2, R2.2, R3.2, R4.2, R5.2, R9.2, R12.1, R14.1, R16.1, R17.1, R22.2, R24.1, R25.2, R26.1, R35.1, R36.2, R44.2, R45.2, R46.2, R47.1, S1.A, S1.B, S2.A, S2.B, SW1.1, U1.8 (VSSA), U1.23 (VSS), U1.35 (VSS), U1.47 (VSS), U2.2 (GND), U3.10 (VSS), U3.20 (VSSA), U3.27 (VSS), U3.74 (VSS), U3.99 (VSS), U4.4 (GND), U6.25 (VSS), U7.4 (GND), U8.4 (GND), U9.2 (GND), U10.1 (GND1), U10.2 (GND1), U10.3 (GND1), U10.5 (GND1), U10.6 (GND1), U10.12 (INV), U10.14 (GND1), U11.8 (GND), U12.4 (GND), U12.5 (A2), U12.6 (A1), U12.7 (A0), U13.1 (A1), U13.2 (A0), U13.7 (GND), U14.9 (GND), U14.19 (GND), Y2.2 (G), Y2.4 (G)
unnamed: BT1.1 (+), D7.2 (A)
unnamed: D1.1 (K), R9.1
unnamed: D2.2 (A), R8.2
unnamed: D5.2 (A), D6.1 (A1), F1.2
unnamed: D8.2 (A), R48.1
unnamed: D9.2 (A), R49.1
unnamed: D10.2 (A), R50.1
unnamed: D11.2 (A), R51.1
unnamed: D12.2 (A), R52.2
unnamed: D13.2 (A), R58.2
unnamed: F1.1, J10.1
unnamed: J2.A5 (CC1), R17.2
unnamed: J2.B5 (CC2), R16.2
unnamed: J3.9, R28.2
unnamed: J3.12, R29.2
unnamed: Q1.1 (B), R10.1, R11.1, R12.2
unnamed: Q1.2 (E), R13.2
unnamed: R7.1, SW2.2 (B)
unnamed: R5.1, R7.2, U1.10 (PA0)
unnamed: R6.2, U1.25 (PB12)
unnamed: R3.1, U1.2 (PC13)
unnamed: R4.1, U1.3 (PC14)
unnamed: C2.1, U1.5 (PD0), Y1.1
unnamed: C3.1, U1.6 (PD1), Y1.2
unnamed: R14.2, U3.94 (BOOT0)
unnamed: C55.2, U3.8 (PC14), Y3.1
unnamed: C54.1, U3.9 (PC15), Y3.2
unnamed: C11.1, U3.49 (VCAP_1)
unnamed: C10.1, U3.73 (VCAP_2)
unnamed: R43.2, U4.6 (CLK)
unnamed: R42.1, U4.7 (~HOLD/~RESET/IO_{3})
unnamed: R41.2, U4.3 (~WP/IO_{2})
unnamed: R22.1, U6.24 (RBIAS)
unnamed: R26.2, U6.10 (RXER/PHYAD0)
unnamed: C24.2, C27.2, U6.6 (VDDCR)
unnamed: C29.2, U6.5 (XTAL1/CLKIN), Y2.1
unnamed: R23.2, U6.14 (~INT/REFCLKO)
unnamed: C41.1, U7.6 (BST)
unnamed: C41.2, L1.1, U7.5 (SW)
unnamed: C42.1, U8.6 (BST)
unnamed: C42.2, L2.1, U8.5 (SW)
unnamed: C62.2, R18.2, S2.C, S2.D, U14.2 (EN)
unnamed: R21.1, U14.16 (IO2)
unnamed: R20.1, U14.7 (IO8)
VBUS: D4.2 (A), J2.A4 (VBUS), J2.A9 (VBUS), J2.B4 (VBUS), J2.B9 (VBUS), R11.2, R58.1, U2.5 (VBUS)

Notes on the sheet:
Flash memory
STLINK - V2
GPIO
SENSOR
RS485
Power - Buck 12V - 5V - 3.3V
ETHERNET - LAN
4 Chanel Relay 12V
WIFI ESP32

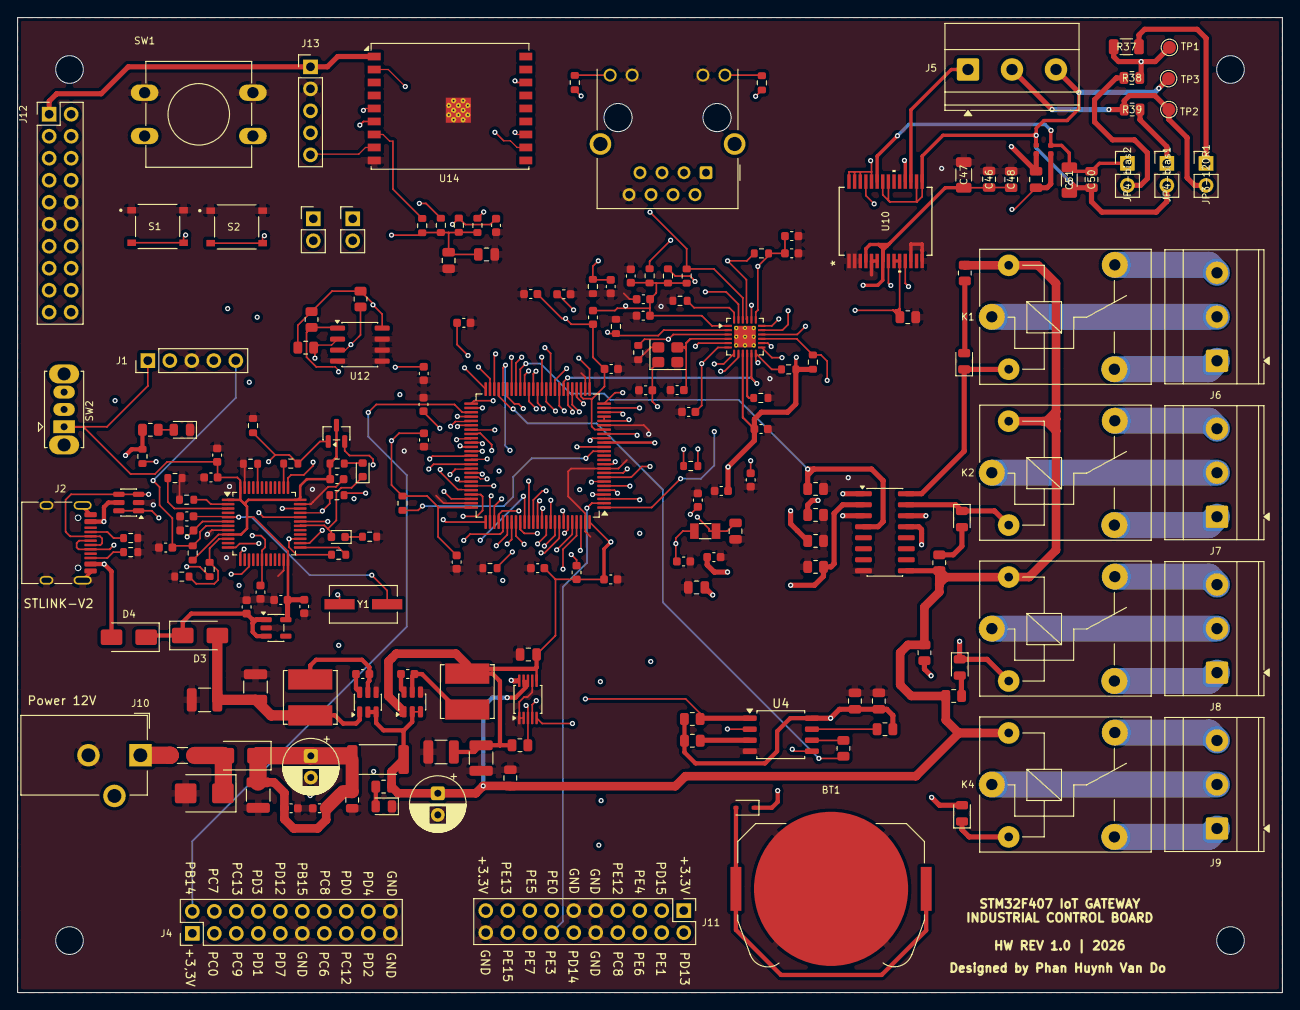
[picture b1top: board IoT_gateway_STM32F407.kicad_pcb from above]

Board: 6 copper layers, 146.1 x 112.6 mm, 191 parts (0 on the bottom side), 180 nets.

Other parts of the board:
H1, H2, H3, H4: MountingHole_3.2mm_M3

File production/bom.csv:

Designator,Footprint,Quantity,Value,LCSC Part #
BT1,BatteryHolder_Keystone_3034_1x20mm,1,Battery_Cell,
"C1, C12, C14, C15, C16, C17, C18, C19, C20, C21, C22, C25, C26, C32, C33, C36, C37, C4, C41, C42, C5, C6, C7",0603,23,100nF,
"C10, C11",0603,2,2.2uF,
"C13, C27, C62",0603,3,1uF,
"C2, C3",0603,2,20pF,
"C23, C8, C9",0603,3,10uF,
C24,0603,1,470pF,
C28,0603,1,4.7uF,
"C29, C30",0603,2,15pF,
C31,0603,1,22nF,
C34,0603,1,1nF,
C35,1210,1,10uF,
"C38, C43, C44, C45",1210,4,22uF,
C39,0805,1,10uF,
"C40, C59",CP_Radial_D6.3mm_P2.50mm,2,47uF,
"C46, C49, C50, C52, C56, C57, C58, C61",0805,8,100nF,
"C47, C51",1206,2,10uF,
"C48, C53, C60",0805,3,1uF,
C54,0603,1,8.2pF,
C55,0805,1,8.2pF,
D1,0603,1,RED,
"D10, D11, D8, D9",0805,4,LED,
D12,0805,1,LED Green,
D13,0805,1,LED Red,
D2,0603,1,BLUE,
"D3, D4",D_SMA,2,SS14,
D5,D_SMA,1,SS34,
D6,D_SMB,1,SMBJ15CA,
D7,D_SOD-323,1,BAS116WS,
F1,1206,1,2A Slow-Blow,
"FB1, FB2",0603,2,FerriteBead,
"FB3, FB4",0402,2,BLM15HD182SN1,
J1,PinHeader_1x05_P2.54mm_Vertical,1,Dùng nạp cho U3,
J10,BarrelJack_CUI_PJ-102AH_Horizontal,1,Power 12V,
J11,PinHeader_2x10_P2.54mm_Vertical,1,GPIO_D_E,
J12,PinHeader_2x10_P2.54mm_Vertical,1,GPIO_A_B,
J13,PinHeader_1x05_P2.54mm_Vertical,1,ESP32_UART0_PROG,
J2,USB_C_Receptacle_HRO_TYPE-C-31-M-12,1,USB_C_Receptacle_USB2.0_16P,
J3,RJ45_Hanrun_HR911105A_Horizontal,1,RJ45_Hanrun_HR911105A_Horizontal,
J4,PinHeader_2x10_P2.54mm_Vertical,1,GPIO_B_C_D,
J5,"TerminalBlock_Phoenix_MKDS-1,5-3-5.08_1x03_P5.08mm_Horizontal",1,Screw_Terminal_01x03,
J6,TerminalBlock_Phoenix_MKDS-3-3-5.08_1x03_P5.08mm_Horizontal,1,RELAY1,
J7,TerminalBlock_Phoenix_MKDS-3-3-5.08_1x03_P5.08mm_Horizontal,1,RELAY2,
J8,TerminalBlock_Phoenix_MKDS-3-3-5.08_1x03_P5.08mm_Horizontal,1,RELAY3,
J9,TerminalBlock_Phoenix_MKDS-3-3-5.08_1x03_P5.08mm_Horizontal,1,RELAY4,
"JP1, JP2, JP3-120R1, JP4-BIAS1, JP4-BIAS2",PinHeader_1x02_P2.54mm_Vertical,5,Jumper_2_Open,
"K1, K2, K3, K4",Relay_SPDT_SANYOU_SRD_Series_Form_C,4,SANYOU_SRD_Form_C,
"L1, L2",L_Bourns_SRN6045TA,2,4.7uH,
Q1,SOT-23,1,BC849,
"R1, R2",0603,2,100k,
"R10, R6",0603,2,100R,
"R11, R14, R15, R18, R19, R20, R21, R24, R25, R26, R27, R3",0603,12,10K,
R12,0603,1,39K,
R13,0603,1,1K5,
"R16, R17",0603,2,5.1K,
R22,0603,1,12.1K,
R23,0603,1,33R,
"R28, R29",0603,2,330R,
"R30, R31, R32, R33",0603,4,49.9R,
R34,0603,1,1.5K,
R35,0603,1,1MR,
"R36, R40, R41, R42, R55, R57",0805,6,10K,
R37,1206,1,120R,
"R38, R39",0805,2,330R,
R4,0603,1,DNP,
R43,0805,1,22R,
"R44, R45, R46, R47",0805,4,100K,
"R48, R49, R50, R51, R52, R53, R54",0805,7,4.7K,
"R5, R7",0603,2,4K7,
R56,2512,1,20mR,
R58,0805,1,1K,
R8,0603,1,200R,
R9,0603,1,220R,
"S1, S2",SW_TS-1187A-B-A-B,2,TS-1187A-B-A-B,
SW1,SW_PUSH-12mm,1,SW_Push,
SW2,SW_Slide_SPDT_Straight_CK_OS102011MS2Q,1,SW_SPDT,
"TP1, TP2, TP3",TestPoint_Pad_D1.5mm,3,TestPoint,
U1,LQFP-48_7x7mm_P0.5mm,1,STM32F103CBTx,
U10,RN-28-1_ADI-L,1,ADM2861EBRNZ,
U11,SOIC-16_3.9x9.9mm_P1.27mm,1,ULN2003A,
U12,SO-8_3.9x4.9mm_P1.27mm,1,TMP1075D,
U13,TSSOP-10_3x3mm_P0.5mm,1,INA226,
U14,ESP32-C3-WROOM-02U,1,ESP32-C3-WROOM-02U,
U2,SOT-23-6,1,USBLC6-2SC6,
U3,LQFP-100_14x14mm_P0.5mm,1,STM32F407VGTx,
U4,SOIC-8_5.3x5.3mm_P1.27mm,1,W25Q128JVS,
U6,VQFN-24-1EP_4x4mm_P0.5mm_EP2.5x2.5mm_ThermalVias,1,LAN8720A,
U7,TSOT-23-6,1,AP63203WU,
U8,TSOT-23-6,1,AP63205WU,
U9,SOT-23-5,1,AP2112K-3.3,
Y1,Crystal_SMD_ECS_CSM3X-2Pin_7.6x4.1mm,1,Crystal,
Y2,Crystal_SMD_3225-4Pin_3.2x2.5mm,1,25MHz,
Y3,Crystal_SMD_3215-2Pin_3.2x1.5mm,1,FC-135,
